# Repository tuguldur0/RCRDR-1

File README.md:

These are the files for my macropad, RCRDR-1. My very first time using KiCad, Shapr3D so it's bound to be a little rough around the edges. 

What's RCRDR-1?
- RCRDR-1 is a macropad that can record and playback whatever you do on your keyboard.

What can you use it for?
- Just about anything! Visual Studio Code shortcuts, AI shortcuts etc. 

Will you update it in the future?
- Probably not, as I plan to make a full keyboard later this month.

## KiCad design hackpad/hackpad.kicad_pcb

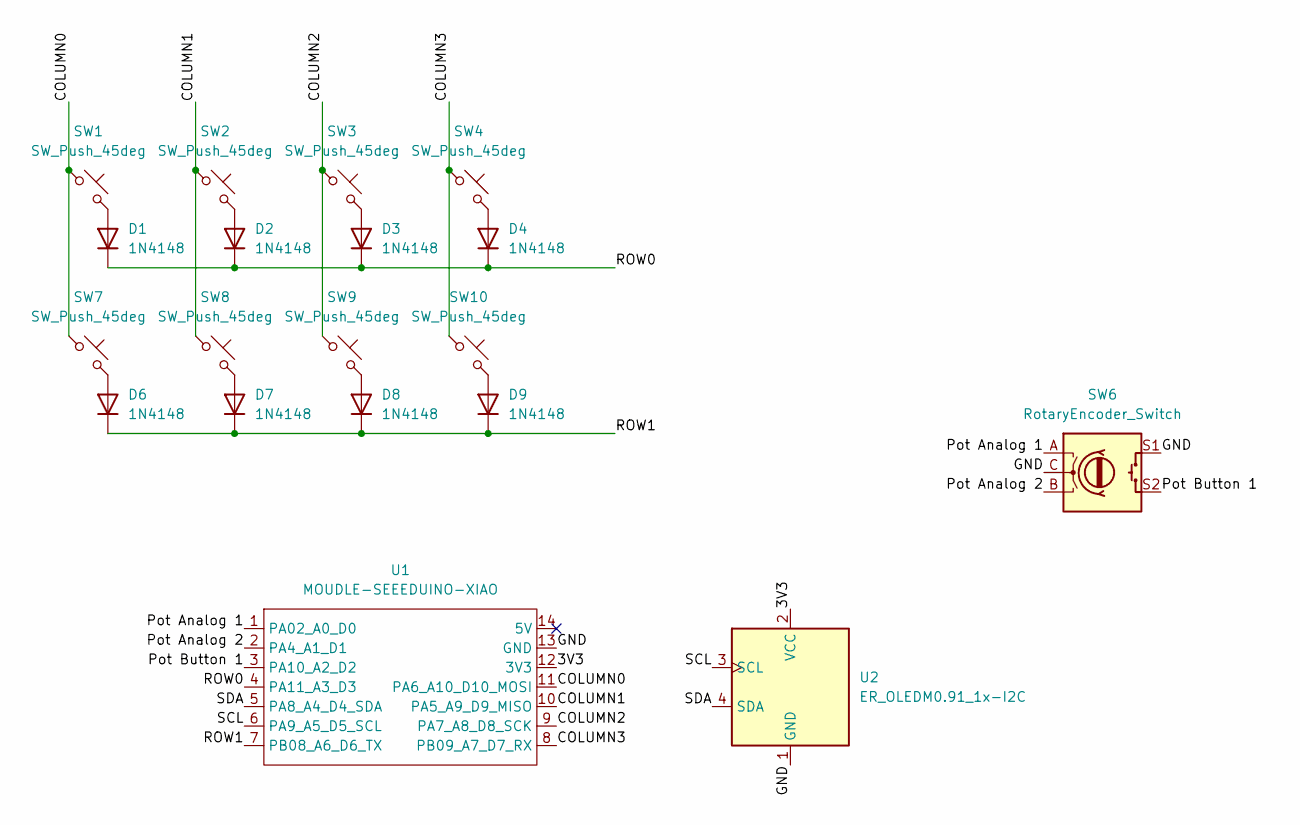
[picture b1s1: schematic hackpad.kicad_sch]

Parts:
D1, D2, D3, D4, D6, D7, D8, D9: 1N4148; D_DO-35_SOD27_P7.62mm_Horizontal
SW1, SW2, SW3, SW4, SW7, SW8, SW9, SW10: SW_Push_45deg; SW_Cherry_MX_1.00u_PCB
SW6: RotaryEncoder_Switch; RotaryEncoder_Alps_EC11E-Switch_Vertical_H20mm
U1: MOUDLE-SEEEDUINO-XIAO; XIAO-Generic-Hybrid-14P-2.54-21X17.8MM
U2: ER_OLEDM0.91_1x-I2C

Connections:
/3V3: U1.12 (3V3), U2.2 (VCC)
/COLUMN0: SW1.1, SW7.1, U1.11 (PA6_A10_D10_MOSI)
/COLUMN1: SW2.1, SW8.1, U1.10 (PA5_A9_D9_MISO)
/COLUMN2: SW3.1, SW9.1, U1.9 (PA7_A8_D8_SCK)
/COLUMN3: SW4.1, SW10.1, U1.8 (PB09_A7_D7_RX)
/GND: SW6.C, SW6.S1, U1.13 (GND), U2.1 (GND)
/Pot Analog 1: SW6.A, U1.1 (PA02_A0_D0)
/Pot Analog 2: SW6.B, U1.2 (PA4_A1_D1)
/Pot Button 1: SW6.S2, U1.3 (PA10_A2_D2)
/ROW0: D1.1 (K), D2.1 (K), D3.1 (K), D4.1 (K), U1.4 (PA11_A3_D3)
/ROW1: D6.1 (K), D7.1 (K), D8.1 (K), D9.1 (K), U1.7 (PB08_A6_D6_TX)
/SCL: U1.6 (PA9_A5_D5_SCL), U2.3 (SCL)
/SDA: U1.5 (PA8_A4_D4_SDA), U2.4 (SDA)
unnamed: D1.2 (A), SW1.2
unnamed: D2.2 (A), SW2.2
unnamed: D3.2 (A), SW3.2
unnamed: D4.2 (A), SW4.2
unnamed: D6.2 (A), SW7.2
unnamed: D7.2 (A), SW8.2
unnamed: D8.2 (A), SW9.2
unnamed: D9.2 (A), SW10.2

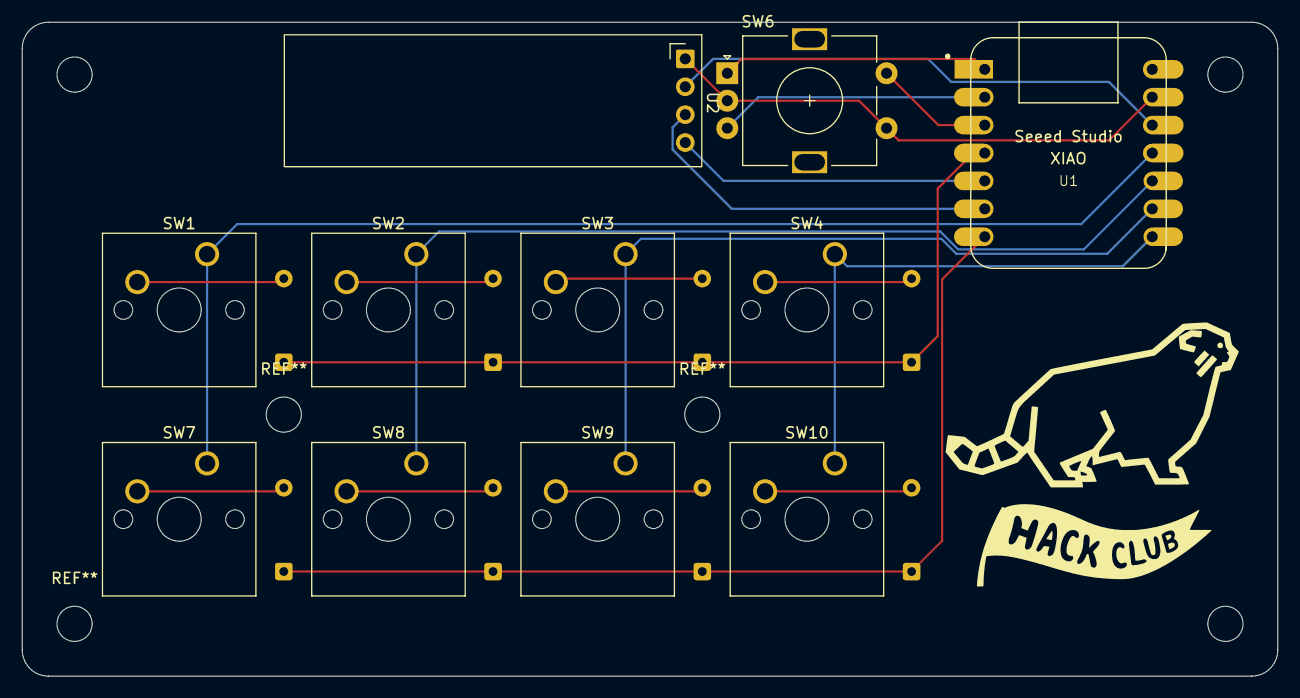
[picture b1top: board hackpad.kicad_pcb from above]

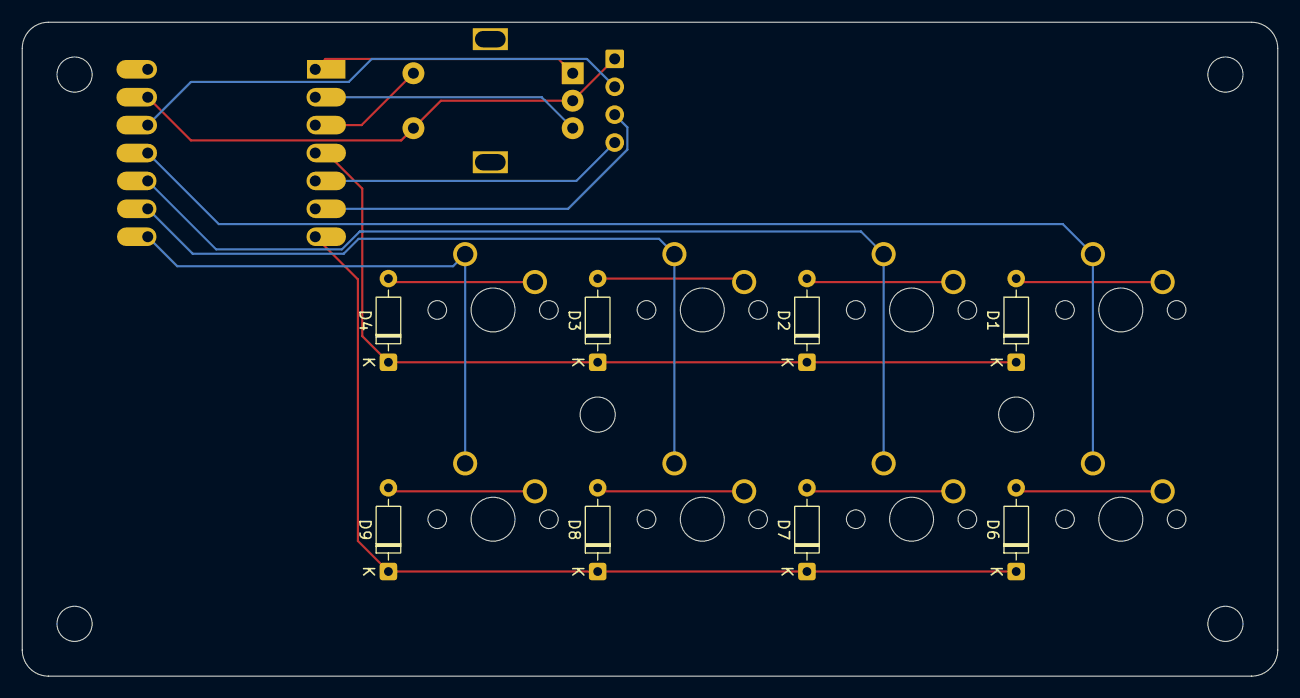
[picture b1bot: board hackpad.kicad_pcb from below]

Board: 2 copper layers, 114.3 x 59.5 mm, 19 parts (8 on the bottom side), 21 nets.
